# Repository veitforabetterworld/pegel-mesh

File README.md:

# pegel-mesh

Wasserstände von entfernten Pegeln per Funk ins Netz, ohne Mobilfunk. Ein Sender am Fluss liest die Pegelsonde (RS485) und funkt über [MeshCore](https://github.com/meshcore-dev/MeshCore) (868 MHz) zu einem Empfänger mit WLAN, der die Werte an die **hochwasserdienst**-API schickt. Der Sender läuft mit Solarpanel und LiFePO4-Akku.

## Platine

Die SMD-Teile bestückt JLCPCB (Dateien in [`hardware/pegel-sender/fab/`](hardware/pegel-sender/fab/)). Selbst löten:

| Teil | Wert | Beispiel |
|---|---|---|
| SOLAR/12V, AKKU | Schraubklemme 2-pol., Raster 5,08 mm | Phoenix MKDS 1,5/2-5,08 |
| SONDE, HEIZ/NTC | Schraubklemme 4-pol., Raster 5,08 mm | Phoenix MKDS 1,5/4-5,08 |
| L1 | Spule 15 µH, ≥ 2,4 A, radial Ø 8,7 mm, Raster 5 mm | Bourns RLB0914-150KL |
| L2 | Spule 10 µH, ≥ 0,5 A, radial Ø 8,7 mm, Raster 5 mm | Bourns RLB0912-100KL |
| C22 | Elko 220 µF 16 V, Polymer oder Low-ESR, Ø 8 mm, Raster 3,5 mm | Panasonic 16SEPF220M |
| C23 | Elko 220 µF 50 V, Low-ESR, Ø 10 mm, Raster 5 mm | Panasonic EEU-FR1H221 |
| XIAO | 2× Buchsenleiste 1×7, 2,54 mm | |
| NETZTEIL | Stiftleiste 1×2, 2,54 mm + Steckbrücke | |

Elkos: Plus an das Pad mit „+“.

Schaltplan: [`hardware/pegel-sender/preview/`](hardware/pegel-sender/preview/) (Blockschaltbild und ein Blatt je Funktionsblock), Technik in [`hardware/pegel-sender/`](hardware/pegel-sender/README.md).

## Anschlüsse

| Klemme | Was |
|---|---|
| **SOLAR/12V** | 12-V-Solarpanel (Leerlauf ≤ 25 V; 10 W Flachland, 30 W Mittelgebirge) **oder** 12-V-Netzteil |
| **AKKU** | LiFePO4, **1 Zelle** (3,2 V), z. B. 2–3 × 6 Ah parallel. 5-A-Sicherung im Pluskabel |
| **HEIZ/NTC** | H+ / H−: Heizwiderstand 68 Ω 10 W; NTC / NTC: Fühler 10 kΩ B3950, **auf den Akku** kleben |
| **SONDE** | V+ rot, V− schwarz, A weiß, B blau. RS485 Modbus RTU, 9600 8N1, Adresse 1, 12 V ≤ 30 mA |
| **NETZTEIL** (Brücke) | gesteckt bei Netzteil, offen bei Solarpanel |

Ohne NTC lädt der Sender nie (gilt als Frost). XIAO nRF52840 mit Wio-SX1262 aufstecken, USB zum Platinenrand („USB ->“); den BAT-Anschluss am XIAO nicht benutzen.

## Installation

Voraussetzungen: Git, Python 3.12+, USB-Treiber für die XIAO-Boards.

```bash
git clone https://github.com/veitforabetterworld/pegel-mesh.git
```

```bash
cd pegel-mesh && git submodule update --init
```

```bash
python3 -m pip install platformio cryptography
```

```bash
python3 tools/genkeys.py
```

`genkeys.py` legt `secrets/` an (nicht im Repo, sicher aufbewahren). Dort von Hand ausfüllen: **`secrets/receiver_wifi.h`** mit WLAN, API-Key (hochwasserdienst: Admin > API-Keys) und Name/Koordinaten der Stationen. Weitere Sender: `python3 tools/genkeys.py A B C`.

Flashen (Port anpassen, unter Windows z. B. `COM5`):

```bash
python3 tools/pio.py run -e pegel_sender_a -t upload --upload-port /dev/ttyACM0
```

| Umgebung | Gerät |
|---|---|
| `pegel_sender_a` | Sender, Messung jede Minute |
| `pegel_sender_b` | Sender, Messung alle 5 min |
| `pegel_receiver` | Empfänger, XIAO ESP32-S3 + Wio-SX1262 |

Immer `tools/pio.py` statt `pio` aufrufen; es hängt `pegel.ini` in das MeshCore-Submodul ein.

## GPS-Tracker

Der Empfänger ist zugleich Gateway für GPS-Tracker: XIAO nRF54LM20A Sense + Wio-SX1262 + L76K-GNSS-Modul (Seeed 109100021). Der Tracker schläft zwischen den Ortungen in System OFF, meldet Position und Akkustand verschlüsselt über MeshCore, speichert nicht quittierte Meldungen zwischen und reicht sie nach. Bei eingeschaltetem Bewegungsalarm weckt ihn der Bewegungssensor. Der Empfänger lädt die Meldungen zu [tracker.plenivo.de](https://tracker.plenivo.de) hoch und gibt dem Tracker dessen Einstellungen (Intervall, Alarm) mit. Firmware in [`firmware/tracker/`](firmware/tracker/), Paketformat in [`firmware/common/tracker_packet.h`](firmware/common/tracker_packet.h).

Schlüssel für einen neuen Tracker (hier `T1`), danach den Empfänger neu flashen:

```bash
python3 tools/genkeys.py --tracker T1
```

In `secrets/receiver_wifi.h` `TRACKER_API_URL` (`https://tracker.plenivo.de/api`) und je Tracker den API-Key aus dem Tracker-Dialog der Webseite eintragen. Ohne URL gibt der Empfänger die Meldungen nur auf Serial aus; Einstellungen lassen sich dann mit `tset <tracker> <intervall 0..3> <alarm 0..3> <alarmintervall 0..3>` auf Serial setzen.

Der nRF54LM20A wird von MeshCore noch nicht offiziell unterstützt; der Tracker baut gegen das Submodul `MeshCore-nrf54` (MeshCore-PR #3530). `tools/pio.py` wählt es für alle Umgebungen `tracker_*` und hängt `tracker.ini` ein.

```bash
python3 tools/pio.py run -e tracker_t1 -t upload
```

Ein neues Board ist ab Werk gesperrt (APPROTECT): einmal mit OpenOCD über den CTRL-AP löschen und dann `-t bootloader` (Bootloader, SoftDevice, Firmware) flashen; danach reicht `-t upload`. Die USB-Seriell-Brücke des Boards bleibt nach System OFF oft hängen; das Log liegt deshalb zusätzlich im RAM und lässt sich per SWD lesen (weckt den Tracker dabei auf):

```bash
bash tools/tracker_log.sh
```

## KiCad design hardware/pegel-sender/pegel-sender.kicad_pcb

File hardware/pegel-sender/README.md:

# pegel-sender — Trägerplatine (Technik)

Träger für XIAO nRF52840 + Wio-SX1262: Laden aus Solar oder 12-V-Netzteil, LiFePO4 1S, 12 V für die Pegelsonde (nur bei Messung), RS485 zur Sonde, Frostschutz mit Heizung am Akku. Platine 100 × 70 mm, 2 Lagen, für IP65-Gehäuse ~115 × 90 mm. Auslegung und Anschluss für Anwender: [README im Repo-Root](../../README.md).

Bilder: [`preview/`](preview/) — Blockschaltplan (`pegel-sender-schematic-blocks.png`), 3D-Ansichten (`pegel-sender-top.png`, `pegel-sender-bottom.png`) und Schaltplan je Funktionsblock (`schematic-*.png`). Simulation und Prüfung: [`verify/`](verify/README.md).

## Schaltung

| Block | Bauteile | Funktion |
|---|---|---|
| Eingang | J1, D1 SMBJ28A, D2 SS54, C1–C4 | Solar oder Netzteil, Überspannung, Verpolung, kein Rückstrom ins Panel |
| Lader | U1 TPS5430, L1 15 µH, D3, Q1 AO3401A | Abwärtswandler, Konstantspannung 3,50 V über VSENSE (R1/R2); C22 (220 µF mit ESR, wie im TI-Referenzdesign) hält den Regelkreis auch ohne Akku stabil, C23 puffert das Panel; Q1 trennt nachts den Akku vom Wandler |
| Regelung | U2 LM324, U3 HT7550 (5 V), U4 CJ431 (2,5 V) | A: Ladestrom 2,0 A (100 mV an R15‖R16 im Minuspol), B: Panel-Arbeitspunkt 17 V bzw. 9,7 V mit JP2, C: Frost-Ladesperre, D: Heizung. A–C ziehen den Lader über D4/D5 und R3 an VSENSE zurück. Läuft nur, wenn VSOL anliegt |
| Frost | NTC an J4, R17–R22, Q3, Q4 HL2310A | Ladesperre unter ~1,2 °C (frei über ~2,7 °C), Heizung unter ~3,8 °C (aus über ~5,2 °C), Heizung nur aus VSOL |
| Sonde 12 V | U5 TPS61040, L2 10 µH, Q5/Q6 | 12,46 V, nur bei SENS_EN (D0); Q5 trennt die Sonde, solange der Wandler aus ist |
| RS485 | U6 SP3485, Q7, Q8 | versorgt nur bei eingeschalteter Sonde; DI fest auf GND, TX schaltet über Q8 den Treiber (TX low → Leitung „0“), R32/R33 halten im Leerlauf „1“ |
| XIAO | D10 B5819W, J5/J6 | XIAO direkt am Akku über D10 (3V3-Pin), D10 sperrt die 3,3 V aus USB |

| XIAO-Pin | Funktion |
|---|---|
| D1–D5, D8–D10 | Wio-SX1262 |
| D6 / D7 | `Serial1` TX / RX zum SP3485 |
| D0 | Sonde und RS485 ein (HIGH) |
| 3V3 | Versorgung aus dem Akku über D10; die Firmware misst VDD und rechnet 0,2 V für D10 dazu |

BAT am XIAO bleibt unbenutzt: der eingebaute Li-Ion-Lader darf die LiFePO4-Zellen nicht sehen.

Alle SMD-Teile stammen aus der JLCPCB-Basic- bzw. Preferred-Bibliothek (LCSC-Nummern in `design.py`), Spulen, Klemmen und Buchsen sind Durchsteckteile zum Selbstlöten.

## Platine und Schaltplan erzeugen

**Software:** [KiCad 10](https://www.kicad.org/download/), **Java (JRE)** für [Freerouting 2.5](https://github.com/freerouting/freerouting/releases) (`build/freerouting.jar`, nicht versionieren).

| Plattform | KiCad |
|---|---|
| Linux (Arch/Manjaro) | `pacman -S kicad kicad-library jre-openjdk` |
| Linux (ohne root) | KiCad-AppImage nach `build/kicad-appimage/` ([Download](https://www.kicad.org/download/linux/)); beim ersten Lauf extrahiert [`kicad_env.py`](kicad_env.py) `squashfs-root` |
| Windows | KiCad-Installer; `kicad_env.py` findet KiCad-Python und `kicad-cli.exe` unter `%LOCALAPPDATA%\Programs\KiCad` bzw. `Program Files\KiCad`. Schaltplan-PNGs: `py -m pip install pymupdf` (statt `rsvg-convert`) |

In diesem Verzeichnis:

1. `python3 design.py` — Netzliste prüfen
2. KiCad-Python: `gen_pcb.py`
3. `route.py build/freerouting.jar` — DRC: 0 offen, 0 Kurzschluss/Kreuzung/Abstandsfehler, 0 Siebdruck-Verstöße
4. `export.py` — Gerber, JLCPCB-BOM/CPL (nur SMD mit LCSC-Nummer) und Liste der Handbestückung nach `fab/`
5. `render_preview.py` — 3D-Bilder nach `preview/`
6. `schematic_blocks.py` — Blockschaltplan; `schematic.py` — Schaltplan je Funktionsblock, gegen die KiCad-Netzliste geprüft

**Platine neu erzeugen:** `python3 relayout.py` (Schritte 2–5). Bauteilpositionen stehen in `fixed_positions.py`; nach manueller Verschiebung in KiCad: KiCad-Python `dump_fixed.py` → `fixed_positions.py` aktualisieren, dann `relayout.py`. Bahnbreiten und Abstände je Netz: `NET_WIDTH`/`HV_NETS` in `gen_pcb.py`; rechte Winkel werden nach dem Routen zu 45°-Schrägen (`route.py`).

**Nur Siebdruck** auf gültiger Platine: KiCad-Python `gen_pcb.layout_silk(board)` speichern, dann `render_preview.py`.

Schaltplan-Grafiken: [`schematic.py`](schematic.py) — Lage der Bauteile je Blatt in [`schematic_layout.py`](schematic_layout.py) (Signalfluss links → rechts, Versorgung oben, Masse unten), Leitungen verlegt ein rechtwinkliger Router; Labels nur für Netze, die das Blatt verlassen. Symbolzugriff in `sch_symbols.py`.

Vor der Bestellung den Abstand der XIAO-Buchsen am realen Stapel messen (Soll 15,24 mm Reihenabstand). In der JLCPCB-Vorschau die Drehung von U1 (TPS5430), U2 (LM324), U3 (HT7550) und den Dioden prüfen: KiCad und JLCPCB zählen Pin 1 nicht immer gleich.

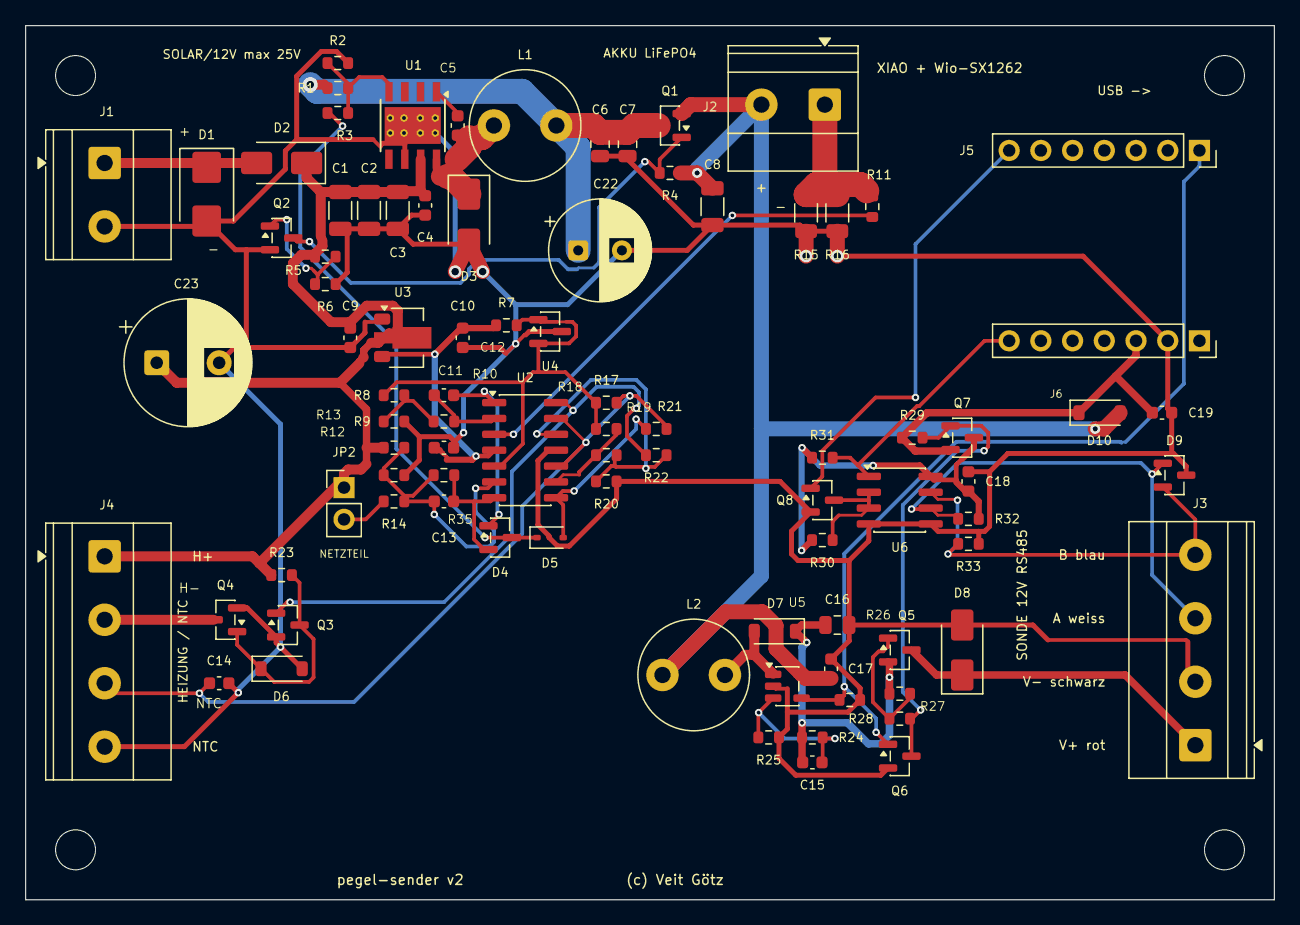
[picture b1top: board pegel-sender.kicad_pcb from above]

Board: 2 copper layers, 100.0 x 70.0 mm, 92 parts (0 on the bottom side), 42 nets.

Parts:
C1, C2, C3: 10uF 50V; C_1206_3216Metric
C4, C11, C12, C14, C18: 100nF; C_0603_1608Metric
C5: 10nF; C_0603_1608Metric
C6, C7: 22uF 25V; C_0805_2012Metric
C8: 100uF 6.3V; C_1206_3216Metric
C9, C10: 1uF; C_0603_1608Metric
C13: 100pF; C_0603_1608Metric
C15: 22pF; C_0603_1608Metric
C16: 10uF 25V; C_0805_2012Metric
C17, C19: 10uF 10V; C_0603_1608Metric
C22: 220uF 16V; CP_Radial_D8.0mm_P3.50mm
C23: 220uF 50V; CP_Radial_D10.0mm_P5.00mm
D1: SMBJ28A; D_SMB
D2, D3: SS54; D_SMA
D4: BAV70; SOT-23
D5: 1N4148WS; D_SOD-323
D6: 10V; D_SOD-123
D7: B0540W; D_SOD-123
D8: SMAJ18A; D_SMA
D9: PSM712; SOT-23
D10: B5819W; D_SOD-123
H1, H2, H3, H4: M3; MountingHole_3.2mm_M3
J1: SOLAR / 12V; TerminalBlock_Phoenix_MKDS-1,5-2-5.08_1x02_P5.08mm_Horizont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
J2: AKKU 3,2V; TerminalBlock_Phoenix_MKDS-1,5-2-5.08_1x02_P5.08mm_Horizont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
J3: SONDE V+ V- A B; TerminalBlock_Phoenix_MKDS-1,5-4-5.08_1x04_P5.08mm_Horizont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
J4: HEIZ NTC; TerminalBlock_Phoenix_MKDS-1,5-4-5.08_1x04_P5.08mm_Horizont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
J5: XIAO D0-D6; PinSocket_1x07_P2.54mm_Vertical
J6: XIAO 5V-D7; PinSocket_1x07_P2.54mm_Vertical
JP2: NETZTEIL; PinHeader_1x02_P2.54mm_Vertical
L1: 15uH; L_Radial_D8.7mm_P5.00mm_Fastron_07HCP
L2: 10uH; L_Radial_D8.7mm_P5.00mm_Fastron_07HCP
Q1, Q5, Q7: AO3401A; SOT-23
Q2, Q3, Q6, Q8: 2N7002; SOT-23
Q4: HL2310A; SOT-23
R1, R25: 56k; R_0603_1608Metric
R2: 30k; R_0603_1608Metric
R3, R10, R30, R32, R33: 10k; R_0603_1608Metric
R4, R5, R23, R26, R27, R28, R29, R31: 100k; R_0603_1608Metric
R6, R18: 47k; R_0603_1608Metric
R7, R9, R11: 1k; R_0603_1608Metric
R8: 24k; R_0603_1608Metric
R12, R14: 300k; R_0603_1608Metric
R13: 51k; R_0603_1608Metric
R15, R16: 0.1; R_1206_3216Metric
R17: 27k; R_0603_1608Metric
R19: 5.1k; R_0603_1608Metric
R20: 49.9k; R_0603_1608Metric
R21, R35: 1M; R_0603_1608Metric
R22: 2M; R_0603_1608Metric
R24: 510k; R_0603_1608Metric
U1: TPS5430; TI_SO-PowerPAD-8_ThermalVias
U2: LM324; SOIC-14_3.9x8.7mm_P1.27mm
U3: HT7550-1; SOT-89-3
U4: CJ431; SOT-23
U5: TPS61040; SOT-23-5
U6: SP3485EN; SOIC-8_3.9x4.9mm_P1.27mm

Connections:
+5V: C10.1, C11.1, R7.1, U2.4, U3.3
BAT_N: J2.1, R11.1, R15.1, R16.1
BST_FB: C15.2, R24.2, R25.1, U5.3
BST_SW: D7.2, L2.2, U5.1
CC_INT: C12.1, R10.2, U2.2
CC_OUT: C12.2, D4.1, U2.1
CC_SENSE: R11.2, U2.3
CC_SET: R8.2, R9.1, R10.1
CHG_BOOT: C5.1, U1.1
CHG_FB: R1.2, R2.1, R3.2, U1.4
CHG_INH: D5.2, R21.1, U2.8
CHG_LIM: D4.3, D5.1, R3.1
CHG_OUT: C6.1, C7.1, C22.1, L1.2, Q1.3, R1.1
CHG_PG: Q1.1, Q2.3, R4.1
CHG_PGD: Q2.1, R5.2, R6.1
CHG_SW: C5.2, D3.1, L1.1, U1.8
GND: C1.2, C2.2, C3.2, C4.2, C6.2, C7.2, C8.2, C9.2, C10.2, C11.2, C14.2, C16.2, C17.2, C18.2, C19.2, C22.2, C23.2, D1.2, D3.2, D6.2, D8.2, D9.3, J1.2, J3.2, J4.4, J6.2, Q2.2, Q3.2, Q4.2, Q6.2, Q8.2, R2.2, R6.2, R9.2, R13.2, R15.2, R16.2, R20.2, R25.2, R26.2, R33.2, U1.6, U1.9, U2.11, U3.1, U4.3, U5.2, U6.4, U6.5
HEAT_G: D6.1, Q3.3, Q4.1, R23.2
HEAT_N: J4.2, Q4.3
HEAT_OFF: Q3.1, R22.1, U2.14
IN_RAW: D1.1, D2.2, J1.1
PSW_G: Q5.1, R27.2, R28.1
PSW_PD: Q6.3, Q7.1, R28.2, R29.2
RS485_A: D9.1, J3.3, R32.1, U6.6
RS485_B: D9.2, J3.4, R33.1, U6.7
RS_DE: Q8.3, R30.2, U6.2, U6.3
RS_VCC: C18.1, Q7.3, R30.1, R31.1, R32.2, U6.8
SENS_EN: J5.1, Q6.1, R26.1, U5.4
T_NTC: C14.1, J4.3, R17.2, R21.2, U2.10, U2.13
T_REF0: R18.2, R19.1, U2.9
T_REF2: R19.2, R20.1, R22.2, U2.12
UART_RX: J6.7, R31.2, U6.1
UART_TX: J5.7, Q8.1
V12_PROBE: D8.1, J3.1, Q5.3
V12_RAW: C15.1, C16.1, D7.1, Q5.2, R24.1, R27.1
VIN_DIV: C13.1, R12.2, R13.1, R14.2, R35.1, U2.6
VIN_J: JP2.2, R14.1
VIN_OUT: C13.2, D4.2, R35.2, U2.7
VREF: R7.2, R8.1, R17.1, R18.1, U2.5, U4.1, U4.2
VSOL: C1.1, C2.1, C3.1, C4.1, C9.1, C23.1, D2.1, J4.1, JP2.1, R5.1, R12.1, R23.1, U1.7, U3.2
VSYS: C8.1, C17.1, D10.2, J2.2, L2.1, Q1.2, R4.2, U5.5
XIAO_3V3: C19.1, D10.1, J6.3, Q7.2, R29.1

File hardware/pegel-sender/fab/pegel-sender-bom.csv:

Comment,Designator,Footprint,LCSC Part #
SMBJ28A,D1,D_SMB,C19077582
SS54,"D2,D3",D_SMA,C22452
10uF 50V,"C1,C2,C3",C_1206_3216Metric,C13585
TPS5430,U1,TI_SO-PowerPAD-8_ThermalVias,C9864
100nF,"C4,C11,C12,C14,C18",C_0603_1608Metric,C14663
10nF,C5,C_0603_1608Metric,C57112
22uF 25V,"C6,C7",C_0805_2012Metric,C45783
56k,"R1,R25",R_0603_1608Metric,C23206
30k,R2,R_0603_1608Metric,C22984
10k,"R3,R10,R30,R32,R33",R_0603_1608Metric,C25804
AO3401A,"Q1,Q5,Q7",SOT-23,C15127
100k,"R4,R5,R23,R26,R27,R28,R29,R31",R_0603_1608Metric,C25803
2N7002,"Q2,Q3,Q6,Q8",SOT-23,C8545
47k,"R6,R18",R_0603_1608Metric,C25819
100uF 6.3V,C8,C_1206_3216Metric,C15008
HT7550-1,U3,SOT-89-3,C16106
1uF,"C9,C10",C_0603_1608Metric,C15849
LM324,U2,SOIC-14_3.9x8.7mm_P1.27mm,C71035
CJ431,U4,SOT-23,C3113
1k,"R7,R9,R11",R_0603_1608Metric,C21190
24k,R8,R_0603_1608Metric,C23352
300k,"R12,R14",R_0603_1608Metric,C23024
51k,R13,R_0603_1608Metric,C23196
1M,"R35,R21",R_0603_1608Metric,C22935
100pF,C13,C_0603_1608Metric,C14858
BAV70,D4,SOT-23,C68978
1N4148WS,D5,D_SOD-323,C2128
0.1,"R15,R16",R_1206_3216Metric,C25334
27k,R17,R_0603_1608Metric,C22967
5.1k,R19,R_0603_1608Metric,C23186
49.9k,R20,R_0603_1608Metric,C23184
2M,R22,R_0603_1608Metric,C22976
10V,D6,D_SOD-123,C19077408
HL2310A,Q4,SOT-23,C7420347
TPS61040,U5,SOT-23-5,C7722
B0540W,D7,D_SOD-123,C7420325
510k,R24,R_0603_1608Metric,C23192
22pF,C15,C_0603_1608Metric,C1653
10uF 25V,C16,C_0805_2012Metric,C15850
10uF 10V,"C17,C19",C_0603_1608Metric,C19702
SMAJ18A,D8,D_SMA,C19077538
SP3485EN,U6,SOIC-8_3.9x4.9mm_P1.27mm,C8963
PSM712,D9,SOT-23,C32677
B5819W,D10,D_SOD-123,C64885

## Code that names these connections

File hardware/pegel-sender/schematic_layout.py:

"""Lage der Bauteile im Schaltplan je Funktionsblock (Einheit 2,54 mm, y nach unten).

parts:  Ref (bei mehreren Einheiten "Ref:Einheit") -> (x, y, Drehung[, "m"]); "m" spiegelt links/rechts.
        Zweipole: R/C/L/Sicherung/NTC stehen bei 0° senkrecht (Pin 1 oben), Dioden liegen bei 0° waagrecht
        (Pin 1 = Kathode links); 90° dreht gegen den Uhrzeigersinn.
power:  (Netz, x, y) Versorgungs- bzw. GND-Symbol; alle Pins des Netzes werden dorthin verdrahtet.
        Ohne Eintrag bekommt jeder Pin ein eigenes Symbol.
labels: (Netz, x, y, Richtung des Texts L/R/U/D) für Netze, die das Blatt verlassen.
fields_left: Zweipole mit Bezeichnung links statt rechts.
"""

GROUPS = [
    ("solar", "Eingang"),
    ("charger", "Lader"),
    ("mppt", "Regelung"),
    ("battery", "Akku"),
    ("frost", "Frost"),
    ("12v", "Sonde 12 V"),
    ("rs485", "RS485"),
    ("xiao", "XIAO"),
]

LAYOUT = {
    # Klemme → TVS nach Masse → Verpolschutzdiode → VSOL mit Eingangskondensatoren
    "solar": {
        "parts": {
            "J1": (0, 0, 0, "m"),
            "D1": (6, 1.5, 270),
            "D2": (10.5, 0, 180),
            "C1": (15, 3.5, 0), "C2": (19.5, 3.5, 0), "C3": (24, 3.5, 0), "C23": (28.5, 3.5, 0),
        },
        "power": [("VSOL", 31, 0), ("GND", 4, 5)],
    },
    # VSOL → TPS5430 → Schaltknoten (D3 nach Masse) → L1 → CHG_OUT → Q1 (Rückstromsperre) → VSYS.
    # VSENSE mit Teiler R1/R2, darüber speist die Regelung über R3 (CHG_LIM) ein.
    "charger": {
        "parts": {
            "C4": (1, 7, 0),
            "U1": (9, 6, 0),
            "C5": (16, 2, 90),
            "D3": (18.5, 9, 270),
            "L1": (22, 4, 90),
            "C6": (24.5, 7.5, 0), "C7": (28.5, 7.5, 0), "C22": (32.5, 7.5, 0),
            "R1": (38, 7.5, 0), "R2": (38, 11, 0), "R3": (41, 12.5, 90),
            "Q1": (45.5, 4, 180, "m"),
            "R4": (49, 7, 0), "Q2": (49, 12, 0),
            "R5": (53.5, 9, 0), "R6": (53.5, 13, 0),
            "C8": (57, 7.5, 0),
        },
        "power": [("VSOL", 1, 3), ("VSYS", 57, 3), ("VSOL", 53.5, 6)],
        "labels": [("CHG_LIM", 44, 12.5, "R")],
        "fields_left": {"C4"},
    },
    # 5 V (HT7550) und 2,5 V (CJ431) aus VSOL. LM324: A Ladestrom (Shunt gegen VREF/25), B Panel-Arbeitspunkt,
    # C Ladesperre, D Heizung. A/B/C ziehen über D4/D5 den Lader zurück (CHG_LIM).
    "mppt": {
        "parts": {
            "C9": (0, 4.5, 0), "U3": (4, 2, 0), "C10": (9, 4.5, 0),
            "R7": (12.5, 4, 0), "U4": (12.5, 9, 0),
            "R8": (17, 4, 0), "R9": (17, 8, 0), "R10": (20.5, 6.5, 90), "R11": (20.5, 12.5, 90),
            "U2:1": (26, 9, 0), "C12": (25.5, 5, 90),
            "JP2": (11, 17, 0), "R14": (14.5, 17, 90), "R12": (17.5, 16, 0), "R13": (17.5, 20, 0),
            "U2:2": (26, 20, 0), "C13": (25.5, 16, 90), "R35": (29, 16, 90),
            "D4": (33, 14, 0), "D5": (33, 27, 0),
            "U2:3": (26, 28, 0), "U2:4": (26, 36, 0), "U2:5": (36, 36, 0), "C11": (40, 36, 0),
        },
        "power": [("VSOL", 0, 1), ("VSOL", 11, 14)],
        "labels": [("CHG_LIM", 37, 14, "R"), ("BAT_N", 20.5, 15.5, "D"), ("VREF", 15, 9, "L"),
                   ("T_NTC", 21, 27, "L"), ("T_REF0", 21, 29, "L"), ("T_REF2", 21, 35, "L"),
                   ("CHG_INH", 31, 30, "R"), ("HEAT_OFF", 31, 36, "R")],
    },
    # Akku an J2, Strommessung R15‖R16 im Minuspol
    "battery": {
        "parts": {
            "J2": (10, 0, 0),
            "R15": (4, 4, 0), "R16": (7, 4, 0),
        },
        "power": [("VSYS", 4, -1)],
        "labels": [("BAT_N", 2, 2, "L")],
        "fields_left": {"R15"},
    },
    # NTC an J4 gegen R17 aus VREF, Schwellenkette R18–R20, Mitkopplung R21/R22; Heizung über Q3 → Q4.
    "frost": {
        "parts": {
            "J4": (-6, 5, 0),
            "R17": (0, 3.5, 0), "C14": (3, 8, 0),
            "R18": (8, 3.5, 0), "R19": (8, 7, 0), "R20": (8, 10.5, 0),
            "R21": (13, 4.5, 90), "R22": (13, 10.5, 90),
            "Q3": (21, 11, 0),
            "R23": (25, 6, 0), "D6": (27.5, 12.5, 270),
            "Q4": (32, 11, 0),
        },
        "power": [("VSOL", 25, 2.5), ("VSOL", -2, 1)],
        "labels": [("VREF", 0, 0.5, "U"), ("VREF", 8, 0.5, "U"), ("T_NTC", 4.5, 5.5, "R"), ("CHG_INH", 16, 4.5, "R"),
                   ("HEAT_OFF", 16, 10.5, "R"), ("T_REF0", 10.5, 6, "R"), ("T_REF2", 10.5, 9, "R")],
        "fields_left": {"R17", "R18", "R19", "R20"},
    },
    # VSYS → L2 → Schaltknoten → D7 → V12_RAW; Q5 schaltet auf V12_PROBE, angesteuert über Q6 (SENS_EN).
    "12v": {
        "parts": {
            "C17": (4, 3.5, 0),
            "L2": (10.5, 2, 90),
            "U5": (10, 8, 0),
            "R26": (4, 10.5, 0),
            "D7": (16.5, 2, 180),
            "C16": (20, 3.5, 0),
            "R24": (25, 3.5, 0), "R25": (25, 6.5, 0), "C15": (28.5, 3.5, 0),
            "R27": (37.5, 3.5, 0), "R28": (37.5, 6.5, 0),
            "Q6": (36.5, 11, 0),
            "Q5": (41.5, 4, 180, "m"),
            "D8": (42.5, 7.5, 270),
        },
        "power": [("VSYS", 1, 2)],
        "labels": [("SENS_EN", 1, 9, "L"), ("SENS_EN", 32.5, 11, "L"), ("V12_PROBE", 44.5, 6, "R"),
                   ("PSW_PD", 39.5, 9, "R")],
        "fields_left": {"C17", "R27", "R28"},
    },
    # Q7 versorgt den SP3485 nur bei eingeschalteter Sonde. TX schaltet über Q8 den Treiber (DI fest auf GND),
    # danach Schutz, Ruhepegel, Abschluss und die Klemme zur Sonde.
    "rs485": {
        "parts": {
            "R29": (1, 3.5, 0), "Q7": (7, 3, 180, "m"), "C18": (10, 7, 0),
            "R31": (13, 7, 0), "R30": (16, 7, 0),
            "Q8": (8, 15, 0),
            "U6": (21, 12, 0),
            "R32": (29, 5, 0), "R33": (36, 16.5, 0),
            "D9": (32, 10.5, 270),
            "J3": (44, 6, 0),
        },
        "power": [("XIAO_3V3", 1, 0.5)],
        "labels": [("PSW_PD", -1, 3, "L"), ("UART_TX", 4, 15, "L"), ("UART_RX", 15, 10, "L"),
                   ("V12_PROBE", 42, 5, "L")],
    },
    # XIAO in zwei Buchsenleisten, Versorgung aus dem Akku über D10
    "xiao": {
        "parts": {
            "J5": (12, 6, 0), "J6": (12, 16, 0),
            "D10": (2, 15, 180), "C19": (6, 17.5, 0),
        },
        "power": [("VSYS", -2, 15), ("XIAO_3V3", 6, 12.5)],
        "wires": [("XIAO_3V3", 6, 15, 10, 15), ("XIAO_3V3", 6, 12.5, 6, 15)],
        "labels": [("SENS_EN", 10, 3, "L"), ("UART_TX", 9, 9, "L"), ("UART_RX", 9, 22, "L")],
        "fields_left": {"C19"},
    },
}

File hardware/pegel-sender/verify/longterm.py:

"""Mehrtägige Simulation: Sonne/Nacht, Temperaturverlauf, Laden, Entladen, Ladesperre, Heizung.

Ein durchgehender Transient (Hysterese der Komparatoren bleibt erhalten). Messung und Funk als Mittelwert:
Sonde 30 mA für 2,1 s je Minute aus VSYS über den 12-V-Wandler, Funk 120 mA für 0,38 s je Minute.
"""

import os

import matplotlib

matplotlib.use("Agg")
import matplotlib.pyplot as plt  # noqa: E402

from board import CAPACITY_AS, R_SHUNT, Scenario, settle  # noqa: E402
from ngspice import NgSpice  # noqa: E402

HERE = os.path.dirname(os.path.abspath(__file__))
REPORT = os.path.join(HERE, "report")
DAY = 86400.0

# Mittlere Zusatzlast an VSYS: Sonde 30 mA · 12,46 V / (VSYS · 0,85) + 1 mA SP3485, je Minute 2,1 s
SENS_AVG = "(0.030*12.46/(max(V(N_VSYS),2.5)*0.85) + 0.001)*2.1/60"
XIAO_AVG_MA = 6.0 + 120 * 0.38 / 60

HOUR = f"(time/3600 - 24*floor(time/{DAY}))"
CASES = {
    "winter": dict(days=3, soc=0.30, temp=f"(-6 + 6*sin(2*pi*({HOUR}-9)/24))",
                   sun=f"(0.35*max(0, sin(pi*({HOUR}-8)/8)) * ({HOUR} > 8) * ({HOUR} < 16))"),
    "sommer": dict(days=2, soc=0.30, temp=f"(20 + 8*sin(2*pi*({HOUR}-9)/24))",
                   sun=f"(1.0*max(0, sin(pi*({HOUR}-5)/15)) * ({HOUR} > 5) * ({HOUR} < 20))"),
}
SAVE = ["n_temp", "n_vsys", "n_vsol", "n_soc", "i:vam_bat", "i:vam_heat", "n_bat_n", "n_chg_inh",
        "n_heat_off", "n_xiao_3v3"]


def profile(expr: str, t: float) -> float:
    """Ausdruck in time (wie für SPICE geschrieben) in Python auswerten."""
    import math
    py = expr.replace("time", f"({t})").replace("floor", "math.floor").replace("sin", "math.sin").replace("pi", "math.pi")
    py = py.replace("max(", "max(").replace(">", ">").replace("<", "<")
    return float(eval(py, {"math": math}))


def run(ng, name, cfg, step=1200.0):
    """Quasistatisch: alle 20 min eingeschwungener Zustand, Ladezustand in Python integriert."""
    soc = cfg["soc"]
    keys = ["time", "n_temp", "n_vsys", "n_vsol", "n_soc", "vam_bat#branch", "vam_heat#branch", "n_bat_n",
            "n_chg_inh", "n_heat_off", "n_xiao_3v3"]
    r = {k: [] for k in keys}
    r["failed"] = 0
    t = 0.0
    last = None
    while t <= cfg["days"] * DAY:
        sun = profile(cfg["sun"], t)
        temp = profile(cfg["temp"], t)
        sc = Scenario(name, sun=sun, temp=temp, soc=soc, xiao_ma=XIAO_AVG_MA)
        try:
            v = settle(ng, sc, extra_lines=[f"Bsens_avg N_VSYS 0 I = {SENS_AVG}*min(1,time/10m)"])
            last = v
        except RuntimeError:
            # Startwert konvergiert nicht (Dämmerung, Panel genau an der Einschaltschwelle): Schritt davor nehmen
            r["failed"] += 1
            v = dict(last or {})
        v["time"] = t
        v["n_soc"] = soc
        for k in keys:
            r[k].append(v.get(k, 0.0))
        soc = min(1.0, max(0.0, soc + v["vam_bat#branch"] * step / CAPACITY_AS))
        t += step
    return r


def main():
    ng = NgSpice()
    os.makedirs(REPORT, exist_ok=True)
    lines = ["# Langzeitsimulation", ""]
    for name, cfg in CASES.items():
        r = run(ng, name, cfg)
        h = [t / 3600 for t in r["time"]]
        ichg = [v / R_SHUNT for v in r["n_bat_n"]]
        heat_w = [i * v for i, v in zip(r["vam_heat#branch"], r["n_vsol"])]
        soc = r["n_soc"]
        # Energie: Ladung ins Akku, Heizenergie (Trapez)
        dt = [b - a for a, b in zip(r["time"], r["time"][1:])]
        ah_in = sum(max(i, 0) * d for i, d in zip(r["vam_bat#branch"], dt)) / 3600
        ah_out = sum(-min(i, 0) * d for i, d in zip(r["vam_bat#branch"], dt)) / 3600
        wh_heat = sum(p * d for p, d in zip(heat_w, dt)) / 3600
        lines += [f"## {name.capitalize()} ({cfg['days']} Tage)", "",
                  f"- Schritte ohne Konvergenz (Wert davor übernommen): {r['failed']} von {len(r['time'])}",
                  f"- Ladezustand: {cfg['soc'] * 100:.0f} % → {soc[-1] * 100:.1f} % (min {min(soc) * 100:.1f} %, max {max(soc) * 100:.1f} %)",
                  f"- Geladen: {ah_in:.2f} Ah, entnommen: {ah_out:.2f} Ah",
                  f"- Heizenergie aus dem Panel: {wh_heat:.1f} Wh",
                  f"- VSYS min/max: {min(r['n_vsys']):.2f} / {max(r['n_vsys']):.2f} V, XIAO_3V3 min: {min(r['n_xiao_3v3']):.2f} V",
                  f"- Ladestrom bei Ladesperre (CHG_INH hoch) max: "
                  f"{max([c for c, s in zip(ichg, r['n_chg_inh']) if s > 1.5] or [0]):.3f} A",
                  f"- Akkustrom nachts (Sonne aus) im Mittel: "
                  f"{sum(i for i, v in zip(r['vam_bat#branch'], r['n_vsol']) if v < 5) / max(1, sum(1 for v in r['n_vsol'] if v < 5)) * 1000:.1f} mA",
                  "", f"![{name}](longterm_{name}.png)", ""]
        fig, ax = plt.subplots(4, 1, figsize=(10, 9), sharex=True)
        ax[0].plot(h, r["n_temp"], label="Temperatur [°C]")
        ax[0].plot(h, r["n_vsol"], label="VSOL [V]")
        ax[0].legend(loc="upper right")
        ax[1].plot(h, ichg, label="Ladestrom [A]")
        ax[1].plot(h, r["vam_heat#branch"], label="Heizstrom [A]")
        ax[1].legend(loc="upper right")
        ax[2].plot(h, [s * 100 for s in soc], label="Ladezustand [%]")
        ax[2].legend(loc="upper right")
        ax[3].plot(h, r["n_vsys"], label="VSYS [V]")
        ax[3].plot(h, r["n_chg_inh"], label="Ladesperre", alpha=0.6)
        ax[3].plot(h, r["n_heat_off"], label="HEAT_OFF (hoch = Heizung aus)", alpha=0.6)
        ax[3].legend(loc="upper right")
        ax[3].set_xlabel("Stunden")
        fig.suptitle(f"Langzeit {name}")
        fig.tight_layout()
        fig.savefig(os.path.join(REPORT, f"longterm_{name}.png"), dpi=100)
        plt.close(fig)
        print("\n".join(lines[-9:-3]))
    # Dunkelflaute: Laufzeit ohne Sonne ab voll
    night = XIAO_AVG_MA + (0.030 * 12.46 / (3.25 * 0.85) + 0.001) * 2.1 / 60 * 1000
    lines += [f"## Dunkelflaute", "",
              f"- Mittlerer Akkustrom ohne Sonne ≈ {night:.1f} mA → {CAPACITY_AS / 3600 / night * 1000 / 24:.0f} Tage "
              f"von voll bis leer (18 Ah)", ""]
    with open(os.path.join(REPORT, "longterm.md"), "w", encoding="utf-8") as fh:
        fh.write("\n".join(lines) + "\n")


if __name__ == "__main__":
    main()
